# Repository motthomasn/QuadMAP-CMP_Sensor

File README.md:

# QuadMAP-CMP_Sensor

Iteration of single MAP-CMP_Sensor described: https://github.com/motthomasn/MAP-CMP_Sensor 

Small module combining 4xMAP sensors and engine phase sensor (camshaft posn) for internal combustion engine management on 4-cylinder engines with individual port throttles.

This module was built for my CBR250RRi project. The aim was to allow an aftermarket ECU to achieve 720deg synchronisation or engine phase detection without the use of a physical camshaft position sensor being installed on the engine. 

The board uses NXP pressure sensors to measure the pressure pulses in each port. The pressure signal from cylinder 1 is passed to an LM397 comparator and compared to a reference voltage determined from a fixed voltage divider. 
The output signal from the comparator is normally high but when the pressure signal falls below the reference voltage, the output is pulled low. With the reference voltage set correctly, a reliable "cam position" signal can be achieved at engine idle
consisting of a single pulse per engine cycle.

**Note:** In a port throttled engine, the pressure signal may not be strong enough to produce a reliable signal throughout the engine speed/load range. In my application this is fine as the ECU I am working with (Life Racing F88R) allows the option to 
ignore the engine phase signal once 720deg synchronisation has been achieved. This means that the signal only has to be reliable during starting and idle.

The signals from all four pressure sensors are processed via LMV324 op-amps so that the output is always the minimum of the four individual signals. This ensures a more stable and reliable pressure signal for engine management.

### Sensor Pinout

Mating connector is JST JWPF 04R-JWPF-VSLE-S.

| Pin # | Description |
|:-----:|:------------|
| 1 | CMP Signal |
| 2 | GND |
| 3 | +5V |
| 4 | MAP Signal |

## Breakout Details

A breakout connector is also included to access the individual raw pressure sensors for diagnostics or possibly throttle body balancing. 

**Wire gauge:**	0.35mm2  
**Sheath:**		Raychem DR-25 1/4"  
**Connector:**	DB9 Female. RS 765-9555  
**Wire Length:**	570mm. Case to back of connector

### Breakout Pinout

| Pin # | Description |
|:-----:|:------------|
| 1 | map1 |
| 2 | map2 |
| 3 | map3 |
| 4 | map4 |
| 5 | GND |
| 6 | N/C |
| 7 | N/C |
| 8 | N/C |
| 9 | N/C |

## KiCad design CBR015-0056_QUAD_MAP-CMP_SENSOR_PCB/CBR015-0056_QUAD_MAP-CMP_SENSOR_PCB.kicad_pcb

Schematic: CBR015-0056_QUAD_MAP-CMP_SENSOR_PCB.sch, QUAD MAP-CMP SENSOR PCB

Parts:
C1, C3, C5, C7: 100nF; C_0805_HandSoldering
C2, C4, C6, C8: 47pF; C_0805_HandSoldering
D1: Toshiba_1SS308; SOT-26-5
J1: B04B-JWPF-SK-R; JST_B04B-JWPF-SK-R
J2: DEBUG_CONN; Pin_Header_Straight_1x04_Pitch2.54mm
J3: SYNC_CONN; Socket_Strip_Straight_2x03_Pitch2.00mm
R1: 10K; R_0805_HandSoldering
R2, R3, R4, R5: 51K; R_0805_HandSoldering
R6: 1K; R_0805_HandSoldering
R7: 3.9K; R_0805_HandSoldering
R8: 5.9K; R_0805_HandSoldering
U1: LM397; SOT-23-5_HandSoldering
U2, U3, U4, U5: MPXA6115A; 98ASB17757C
U6: LMV324; SOIC-14_3.9x8.7mm_Pitch1.27mm

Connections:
+5V: C1.1, C3.1, C5.1, C7.1, J1.3, J3.6, R1.1, R6.1, R7.1, U1.5, U2.2, U3.2, U4.2, U5.2, U6.4 (V+)
CMP_SIG: J1.1, J2.2, R1.2, U1.4
Earth: C1.2, C2.1, C3.2, C4.1, C5.2, C6.1, C7.2, C8.1, J1.2, J2.4, J3.5, R2.2, R3.2, R4.2, R5.2, R8.2, U1.2, U2.3, U3.3, U4.3, U5.3, U6.11 (V-)
MAP1_SIG: C2.2, J2.1, J3.1, R2.1, U1.3, U2.4, U6.3 (+)
MAP2_SIG: C4.2, J3.2, R3.1, U3.4, U6.5 (+)
MAP3_SIG: C6.2, J3.3, R4.1, U4.4, U6.10 (+)
MAP4_SIG: C8.2, J3.4, R5.1, U5.4, U6.12 (+)
MAP_SIG: D1.2, J1.4, R6.2, U6.2 (-), U6.6 (-), U6.9 (-), U6.13 (-)
unnamed: D1.1, U6.1
unnamed: D1.3, U6.7
unnamed: D1.4, U6.8
unnamed: D1.5, U6.14
VREF: J2.3, R7.2, R8.1, U1.1

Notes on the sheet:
HARNESS CONNECTOR
CYL #1 PRESSURE SENSOR
COMPARATOR
REF VOLTAGE DIVIDER
DEBUG CONNECTOR
CYL #2 PRESSURE SENSOR
CYL #3 PRESSURE SENSOR
CYL #4 PRESSURE SENSOR
SYNC CONNECTOR
MIN VOLTAGE FILTER

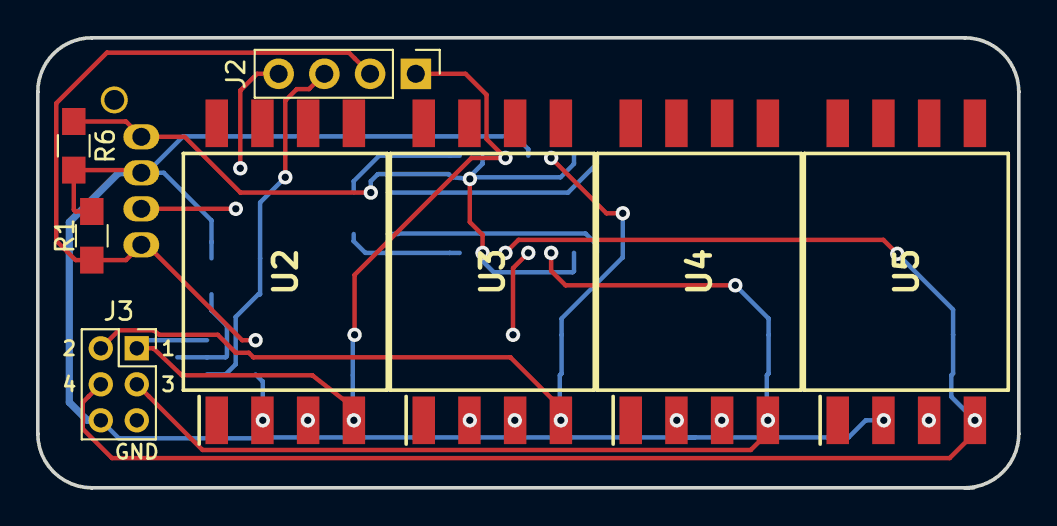
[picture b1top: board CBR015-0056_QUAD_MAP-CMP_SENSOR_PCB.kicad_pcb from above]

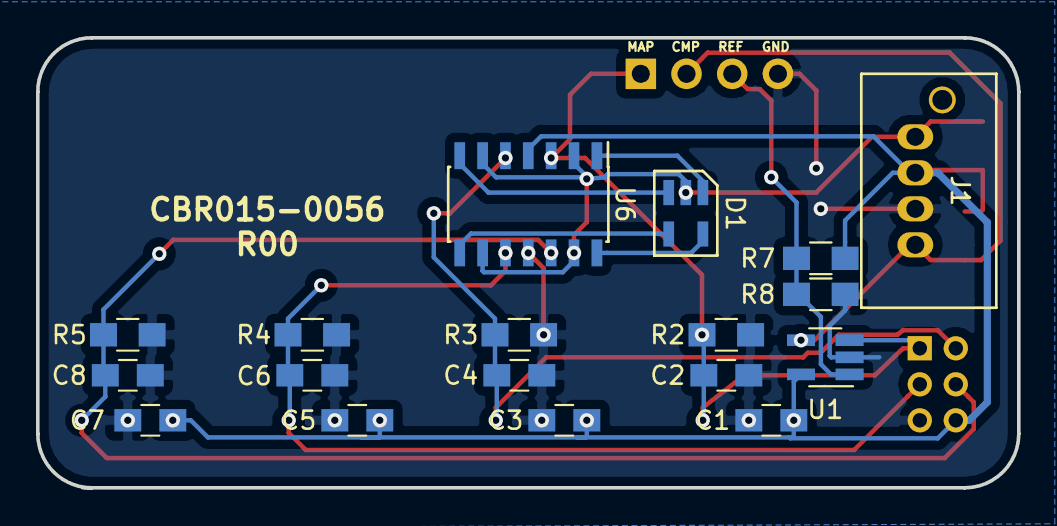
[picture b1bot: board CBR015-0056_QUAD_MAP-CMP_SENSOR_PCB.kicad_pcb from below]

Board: 2 copper layers, 54.5 x 25.0 mm, 26 parts (18 on the bottom side), 13 nets.

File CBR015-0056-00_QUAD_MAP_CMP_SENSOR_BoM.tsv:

Designation	Description	Value	Manufacturer	Part Number	Package	Supplier	Stock No. / Order Code	Purchased	Notes
U1	Comparator	44μs, 30V	Texas Instruments	LM397MF/NOPB	SOT-23	Farnell	3118476	Y	
U2	Pressure Sensor	15-115 kPa	NXP	MPXA6115AC6U		RS	719-1134	Y	
U3	Pressure Sensor	15-115 kPa	NXP	MPXA6115AC6U		RS	719-1134		
U4	Pressure Sensor	15-115 kPa	NXP	MPXA6115AC6U		RS	719-1134		
U5	Pressure Sensor	15-115 kPa	NXP	MPXA6115AC6U		RS	719-1134		
U6	Quad Op-Amp		Texas Instruments	LMV324QD	SOIC-14	RS	732-0910		
J1	Connector	4 way male	JST	B04B-JWPF-SK-R		Farnell	1324127	Y	
J2	Debug Connector	4 way male				RS			Only used to facilitate connection to oscilloscope for initial testing & debug. May be removed in later revisions
J3	Sync Connector	5 way female							
C1	Pressure sensor power smooth cap	100nF	AVX	08055C104KAT2A	805	RS	464-6688		
C2	Pressure sensor output smooth cap	47pF	KEMET	C0805C470J5GACTU	805	RS	264-4270		
C3	Pressure sensor power smooth cap	100nF	AVX	08055C104KAT2A	805	RS	464-6688		
C4	Pressure sensor output smooth cap	47pF	KEMET	C0805C470J5GACTU	805	RS	264-4270		
C5	Pressure sensor power smooth cap	100nF	AVX	08055C104KAT2A	805	RS	464-6688		
C6	Pressure sensor output smooth cap	47pF	KEMET	C0805C470J5GACTU	805	RS	264-4270		
C7	Pressure sensor power smooth cap	100nF	AVX	08055C104KAT2A	805	RS	464-6688		
C8	Pressure sensor output smooth cap	47pF	KEMET	C0805C470J5GACTU	805	RS	264-4270		
R1	Comparator output pull-up resistor	10K	TE Connectivity	CRG0805F10K	805	RS	223-0562		
R2	Pressure sensor output filter resistor	51K	Vishay	CRCW080551K0FKEA	805	RS	679-1525		
R3	Pressure sensor output filter resistor	51K	Vishay	CRCW080551K0FKEA	805	RS	679-1525		
R4	Pressure sensor output filter resistor	51K	Vishay	CRCW080551K0FKEA	805	RS	679-1525		
R5	Pressure sensor output filter resistor	51K	Vishay	CRCW080551K0FKEA	805	RS	679-1525		
R6	Op-Amps Pull-Up Resistor	1K	Bourns	CR0805-FX-1001ELF	805	RS	740-8971		
R7	Ref Voltage Divider	3.9K	TE Connectivity	CRG0805F3K9	805	RS	223-0506		
R8	Ref Voltage Divider	5.9K	TE Connectivity	CPF0805B5K9E1	805	RS	123-3041		
D1		Quad 80V 300mA Common Anode	Toshiba	1SS308(TE85L,F)	SOT-26	RS	579-604

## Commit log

2026-03-31 Initial commit from local
2026-03-31 Remove desktop.ini
2026-04-01 Moved DB9 pinout to README.md file and removed Excel pinout
2026-04-01 Removed .gsheet BoM & replaced with TSV file
2026-04-01 Moved testing screenshots to Testing directory
2026-04-01 Added single port vs min-of-4 ports MAP signal screenshots
